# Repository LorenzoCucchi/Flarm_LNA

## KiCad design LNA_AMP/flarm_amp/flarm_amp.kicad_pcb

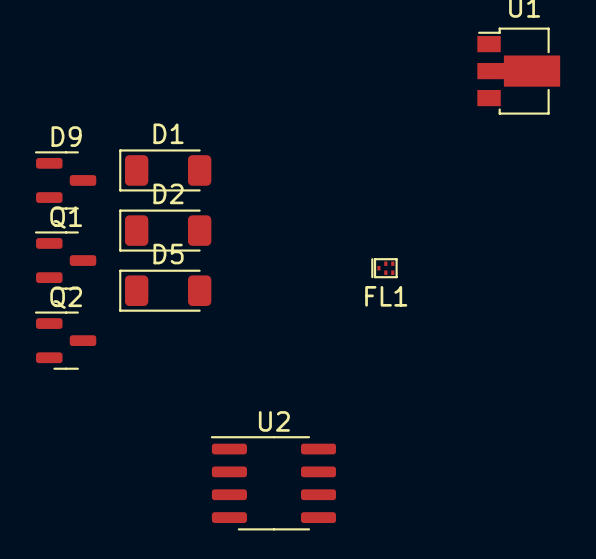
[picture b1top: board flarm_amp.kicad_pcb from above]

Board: 2 copper layers, 9 parts (0 on the bottom side), 5 nets, no tracks yet.

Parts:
D1, D2, D5: LL4148; D_MiniMELF
D9: BAV99; SOT-23
FL1: B39871B3734H110; Filter_1109-5_1.1x0.9mm
Q1: BC817; SOT-23
Q2: IRLML2060; SOT-23
U1: PGA-105; SOT-89-3
U2: LM78L05_SO8; SOIC-8_3.9x4.9mm_P1.27mm

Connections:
GND: D5.2 (A), D9.1 (K), D9.2 (A), FL1.2, FL1.3, FL1.4, FL1.5, Q2.2 (S), U1.2 (GND), U2.2 (GND), U2.3 (GND), U2.6 (GND), U2.7 (GND)
unnamed: D9.3 (K), FL1.1
unnamed: D1.1 (K), D2.1 (K), U2.8 (IN)
unnamed: D5.1 (K), Q1.2 (E)
unnamed: Q1.1 (B), Q2.3 (D)

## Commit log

2023-10-18 first_commit
2023-11-02 friggi scemo
2023-11-02 PDF saw filter
